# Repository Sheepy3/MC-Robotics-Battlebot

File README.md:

[to-do]

~~stole~~ borrowed STEP for XIAO RP2040 from https://grabcad.com/library/seeed-studio-xiao-rp2040-1

# PCB

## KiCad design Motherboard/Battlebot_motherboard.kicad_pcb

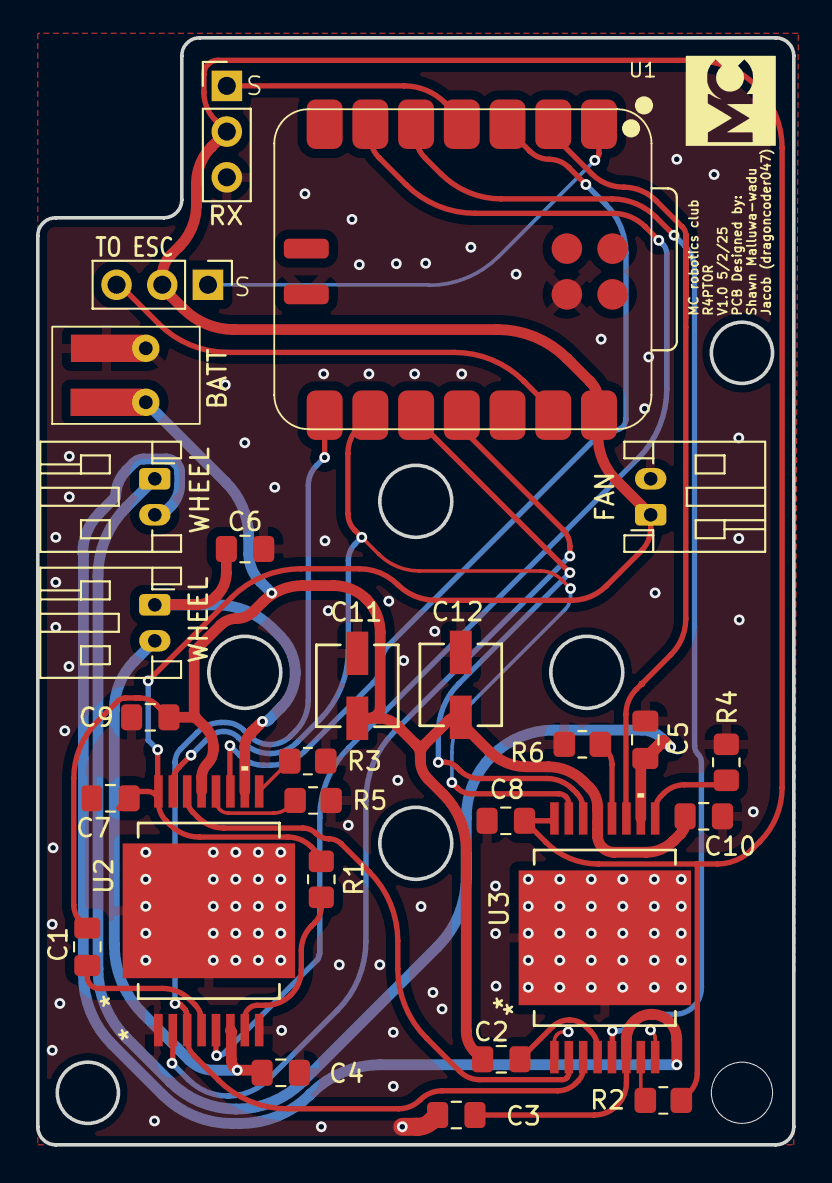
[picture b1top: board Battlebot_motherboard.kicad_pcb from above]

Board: 2 copper layers, 42.0 x 61.5 mm, 27 parts (0 on the bottom side), 27 nets.

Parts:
BATT: 12Vin; 2_Wire
C1, C2, C7, C8: 100nF; C_0805_2012Metric_Pad1.18x1.45mm_HandSolder
C3, C4, C5, C6: 10nF; C_0805_2012Metric_Pad1.18x1.45mm_HandSolder
C9, C10: 1uF; C_0805_2012Metric_Pad1.18x1.45mm_HandSolder
C11, C12: 100uF; CAP_UCD_4X5P8_NCH
FAN: Fan connector; JST_PH_S2B-PH-K_1x02_P2.00mm_Horizontal
R1, R2, R5, R6: 10kohm; R_0805_2012Metric_Pad1.20x1.40mm_HandSolder
R3, R4: 22kohm; R_0805_2012Metric_Pad1.20x1.40mm_HandSolder
RX: Reciever; PinHeader_1x03_P2.54mm_Vertical
TO ESC: BEC; PinHeader_1x03_P2.54mm_Vertical
U1: XIAO-RP2040-SMD
U2, U3: L9958SBTR; POWERSO16_STM
WHEEL: Conn_01x02_Socket; JST_PH_S2B-PH-K_1x02_P2.00mm_Horizontal
WHEEL#2: Conn_01x02_Socket; JST_PH_S2B-PH-K_1x02_P2.00mm_Horizontal

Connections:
1SO: U2.14 (SI), U3.2 (SO)
+5V: C7.1, C8.1, FAN.1, R1.2, R2.2, RX.2, TO ESC.2, U1.14 (5V), U2.16 (VDD), U3.16 (VDD)
+12V: BATT.1, C1.2, C2.2, C9.1, C10.1, C11.1, C12.1, U2.13 (VS), U3.13 (VS)
CS: U1.8 (GPIO1_D7_CSn_RX), U2.3 (CS), U3.3 (CS)
DIR1: U1.5 (GPIO6_D4_SDA), U3.5 (DIR)
DIR2: U1.6 (GPIO7_D5_SCL), U2.5 (DIR)
GND: BATT.2, C3.2, C4.2, C5.1, C6.1, C7.2, C8.2, C9.2, C10.2, C11.2, C12.2, FAN.2, R3.2, R4.2, R5.2, R6.2, RX.3, U1.16 (GND), U1.20 (GND), U2.1 (GND), U2.8 (PGND), U2.EPAD, U3.1 (GND), U3.8 (PGND), U3.EPAD
unnamed: TO ESC.3, U1.13 (GND)
unnamed: C5.2, U3.10 (OUT2), WHEEL#2.1
unnamed: C3.1, U3.6 (OUT1), WHEEL#2.2
unnamed: C6.2, U2.10 (OUT2), WHEEL.1
unnamed: C4.1, U2.6 (OUT1), WHEEL.2
unnamed: C1.1, U2.4 (CP)
unnamed: R1.1, U2.7 (DI)
unnamed: R3.1, U2.9 (EN)
unnamed: R5.1, U2.12 (REXT)
unnamed: C2.1, U3.4 (CP)
unnamed: R2.1, U3.7 (DI)
unnamed: R4.1, U3.9 (EN)
unnamed: R6.1, U3.12 (REXT)
PPM: RX.1, U1.4 (GPIO29_A3_D3)
PWM1: U1.2 (GPIO27_A1_D1), U3.11 (PWM)
PWM2: U1.3 (GPIO28_A2_D2), U2.11 (PWM)
PWM3: TO ESC.1, U1.1 (GPIO26_A0_D0)
SCK: U1.9 (GPIO2_D8_SCK), U2.15 (SCK), U3.15 (SCK)
µSI: U1.11 (GPIO3_D10_MOSI), U2.2 (SO)
µSO: U1.10 (GPIO4_D9_MISO), U3.14 (SI)

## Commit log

2024-09-09 init commit
2025-03-07 all the pcb stuff
2025-03-07 Update schematic which was quite wrong in a number of places
2025-04-05 nightmare routing job
2025-04-05 moved some jumper holes for usb access
2025-04-05 connected more of the ground pours
2025-04-11 reroute using 2 layers and fix 1 connector
2025-04-22 cleaned routing a little bit and updated silkscreen
2025-04-22 fixed ground plane with another via
2025-04-25 change width of a few tracks
2025-04-25 new cap footprint and rerouting for it
2025-04-25 updated silkscreen
2025-04-25 add testing firmware
2025-04-26 update with rounded tracks
2025-04-26 oops traces
2025-04-28 add step model of mobo and symbols
2025-04-29 removed jumper, fixed ground pours as, added 3D models for rp2040 and caps
2025-04-29 Update README.md
    added pretty picture
2025-04-29 updated traces one intersection
2025-04-29 added lck to gitignore
2025-04-29 ok actually fixed now ffs
2025-04-29 moved big caps farther from screws
2025-05-02 copper pads
2025-05-02 fix traces and stuff
2025-05-21 firmware from today
2025-05-27 fix 2 bugs:
    * spi clock frequency was set to 14MHz due to copypasta but per datasheet max is 5Mhz. lowered it to 1Mhz to be safe.
    * correctly set pwm resolution to 9 bit (I was requesting 1024 bit previously wtf??)
2025-05-27 remove turning only when moving code per caleb's request
    somehow I only did that on the xbox side not the radio side too
2025-06-03 stoopid bug write() => writeMicrodeconds()
